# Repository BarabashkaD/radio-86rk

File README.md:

# Radio 86RK
Re-make of the Soviet Ham Radio computer published in Radio Magazine in 1986

## Hardware Documentation

## Table of Content
* [Introduction](#introduction)
* [Specifications](#specifications)
* [Verification](#verification)
* [KiCad 10](#kicad-10)
  * [Prerequisites](#prerequisites)
  * [Mechanical export, for case design](#mechanical-export-for-case-design)
* [Project Notes](#project-notes)
* [Hardware Documentation](#hardware-documentation)
  * [Schematic and PCB Layout](#schematic-and-pcb-layout)
  * [Connectors](#connectors)
  * [Bill of Materials](#bill-of-materials)
  * [Memory Map](#memory-map)
* [Firmware Documentation](#firmware-documentation)
  * [Monitor](#monitor)
* [Release Notes](#release-notes)
  * [Changes](#changes)
  * [Known Issues](#known-issues)

## Introduction
This project is a remake of [Radio-86RK](https://en.wikipedia.org/wiki/Radio-86RK) - a soviet ham radio computer. The original design was published in Radio Magazine, an amateur radio and DIY electronics oriented publication, starting from [April 1986](Radio-86RK_Publications.md). Hence the "Radio" and "86" in the name ("RK" stands for ham radio computer).

The goal of the original design was to create a computer that can be built relatively easily and cheaply using commonly available components. Therefore it included several short-cuts. For example it didn't use 8228 bus controller. Instead, it uses */WR* and *DBIN* CPU signals instead to distinguish between write and read CPU cycles. Since the system doesn't decode I/O control signals, all the I/O devices are memory mapped. Another optimization is the use of DMA controller for both supplying the data to the CRT controller and for refreshing DRAMs. The system didn't support interrupts. The sound was implemented using *INTE* output of the CPU. The software would use **EI**/**DI** instructions to generate sound. There are no graphics capabilities. The font size was limited to 128 characters (8275 CRT controller limitation), and given that it had to support both Latin and Cyrillic ABCs, it only had capital letters for both ABCs. The CRT controller shares 16 MHz clock oscillator with the CPU (not uncommon in other home computers at that time period).

Despite the limitations, the design was fairly successful, many people have built this computer, and there are some that still building one, this project included. In addtion, several factories manufactured computers based on (but not always compatible with) this design - e.g. [Mikrosha](https://oldcomputer.info/8bit/mikrosha/index.htm), [Apogee BK-01](https://ru.wikipedia.org/wiki/%D0%90%D0%BF%D0%BE%D0%B3%D0%B5%D0%B9_%D0%91%D0%9A-01), and a few more.

### Specifications of the Original Design
  * KR580VM80A (Intel 8080) CPU @ 1.78 MHz (16 MHz divided by 9)
  * 16 KiB to 32 KiB DRAM, 2 KiB ROM (monitor software)
  * KR580VG75 (Intel 8275) CRT controller which works together with KR580VT57 (Intel 8257) DMA controller. 1 KiB ROM is used for font
  * Two KR580VV55A (Intel 8255A) PPIs. One is used for keyboard and cassette I/O, another one for the extension port
  * Normally the computer consisted of 2 or 3 PCBs - the mainboard, the keyboard, and the keypad.

### Modifications to the Original Design
 * 16 DRAM ICs replaced with a single 32 KiB SRAM IC
 * Font ROM size increased to 2 KiB, so that it fits an alternative font. CRT controller GPA0 attribute is used to switch between fonts.
 * Reverse video attribute implemented in CRT controller
 * Added 8251 USART and 8253 timer. The timer is used for dividing the clock for USART and for sound generation.
 * Single board design, including an integrated mechanical keyboard
 * The work is largely based on [Radio-86RК-SRAM](http://radio86rk.pbworks.com/w/page/58467718/Radio-86R%D0%9A-SRAM) project created by Alexey Khudyakov (alexcp).

## Specifications
* Processor: Intel 8080A / КР580ВМ80А CPU running at 1.78 MHz
* Memory:
  * RAM: 32 KiB SRAM
  * ROM: 2 KiB UV EPROM with system monitor software
* Video: Intel 8275 / КР580ВГ75 CRT Controller
  * Alphanumeric display
  * 2 KiB UV EPROM with font
  * Composite video output (50 Hz)
* Audio:
  * Intel 8253 / КР580ВИ53 (single channel)
  * CPU INTE output
* Parallel Interface:
  * Intel 8255А / КР580ВВ55А PPI
  * 26-pin expansion header
* Serial Interface:
  * Intel 8251А / КР580ВВ51А USART
  * DE-9 connector
* Built-in 67-keys keyboard
* Cassette recorder interface

## Verification

This repository includes a small, dependency-free harness that proves the
board's copper, connectivity and rule counts have not changed since the
committed baseline. Requires KiCad 10+ and Python 3.8+, no install step:

```
python3 tools/kicad-verify.py all
```

See [`tools/README.md`](tools/README.md) for the full command reference,
exit codes, and how to reuse it on another project.

## KiCad 10

This fork's KiCad files have been modernized to KiCad 10 format. **The board is
unchanged**: the gerber and drill output is identical to skiselev's v1.4, verified
automatically rather than asserted. All footprints and symbols are vendored into the
repository, so the project opens from a fresh clone with no external checkouts.

The rear panel, with every external connector in one row — composite video, serial,
parallel, cassette, sound and power:

Also rendered: [top](images/Radio-86RK-1.4-3D-Top.jpg) ·
[from the right](images/Radio-86RK-1.4-3D-Iso-Right.jpg) ·
[solder side](images/Radio-86RK-1.4-3D-Bottom.jpg), which carries the memory map, the
monitor command list and the subroutine table in silkscreen.

### Prerequisites

* **KiCad 10.0.4** or newer.
* The **Keyswitch Kicad Library**, v2.4, from KiCad's Plugin and Content Manager —
  package `com.github.perigoso.keyswitch-kicad-library`, upstream
  [github.com/kiswitch/keyswitch-kicad-library](https://github.com/kiswitch/keyswitch-kicad-library),
  CC-BY-SA-4.0. It supplies three model files that 69 of this board's 209 model
  references depend on: the Cherry MX switch body shared by all 67 keys, and two
  stabilizers. Without it the board still opens, routes and exports correctly — only the
  keyboard renders empty in the 3D view.

Check that everything resolves before trusting a render:

```
python3 tools/kicad-verify.py models
```

It reports 183 / 183 footprints covered when the library is installed, and names the
path variable responsible when it is not.

- [Modernization summary](docs/modernization-summary.md) — before/after, and how to re-verify
- [3D model sources](docs/3d-model-sources.md) — every model choice and substitution
- [Retained DRC violations](docs/drc-exclusions.md) — the 22 inherited from v1.4
- [Retained ERC violations](docs/erc-exclusions.md) — the 32 bus-label warnings
- [3D model follow-ups](docs/followup-3d-models.md) — the five approximations now resolved, and optional keycaps

### Mechanical export, for case design

```
python3 tools/export_mech.py            # STEP + placement CSV into .build/mech/
```

Writes four STEP files sharing one datum — the whole assembly, the parts needing panel
cutouts, the switches alone, and the bare board with its mounting holes — plus a CSV
giving every footprint's position, rotation, value and package.

Keycaps are deliberately absent. A cap is a case parameter rather than a board one: its
envelope drives the top-plate openings and the bezel height, and comparing profiles should
cost one filename, not a re-export. `placement.csv`'s `Package` column is the cap size, so
all 68 caps can be placed from the table.

## Project Notes

Check [Project Notes](Project_Notes.md) for the information about building this project

## Hardware Documentation

### Documentation for the Previous Versions

* [Version 1.3](https://github.com/skiselev/radio-86rk/tree/v1.3)
* [Version 1.2](https://github.com/skiselev/radio-86rk/tree/v1.2)
* [Version 1.1](https://github.com/skiselev/radio-86rk/tree/v1.1)

### Schematic and PCB Layout

* [Schematic - Version 1.4](KiCad/Radio-86RK-Schematic-1.4.pdf)
* [PCB Layout - Version 1.4](KiCad/Radio-86RK-Board-1.4.pdf)

### Connectors

#### J1 - Composite Video

Pin | Description     
--- | ---------------
Tip (the inner contact) | Output: Composite Video
Ring / Sleeve         |	Power: GND

#### J2 - Power (5V)
Connect regulated +5V power supply to this connector.

Note: The 8080A CPU, clock generator, and serial port transmitters and receivers use +12V/-5V/-12V voltages. An on-board DC-DC converter (U26) is used to obtain these voltages. Instead of using the DC-DC converter it is possible to provide these voltages directly to the system using J3 connector.

Pin | Description     
--- | ---------------
Tip (the inner contact) | Power: 5V (positive terminal)
Barrel / Sleeve         |	Power: GND (negative terminal)

#### J3 - Power (5V, 12V, -12V)
Connect regulated 5V/12V/-12V power supply to this connector.

Pin | Description     
--- | ---------------
1, 2, 3 | Power: GND
4, 5, 6 |	Power: 5V
7   |	Power: 12V
8   |	Power: -12V

#### J4 - Cassette Connector
Pin | Description     
--- | ---------------
1, 2, 3, 8   | Power: GND
4   |	Output: Sound output to cassette recorder (line level)
5   |	Input: Sound input from cassette recorder (line level)
6, 7 |	Not connected

#### J5 - Serial Port Connector
Pin | Description     
--- | ---------------
1   | Not connected: DCD
2   | Input: RX
3   | Output: TX
4   | Output: DTR
5   | Power: GND
6   | Input: DSR
7   | Output: RTS
8   | Input: CTS
9   | Not connected: RI

#### J6 - Parallel Port Connector
Pin | Description | Pin | Description
--- | ----------- | --- | ----------------
1   | Output: PC0 | 2   | Input: PA0
3   | Output: PC1 | 4   | Input: PA1
5   | Output: PC2 | 6   | Input: PA2
7   | Output: PC3 | 8   | Input: PA3
9   | Output: PC4 | 10  | Input: PA4
11  | Output: PC5 | 12  | Input: PA5
13  | Output: PC6 | 14  | Input: PA6
15  | Output: PC7 | 16  | Input: PA7
17  | Output: PB7 | 18  | Output: PB0
19  | Output: PB6 | 20  | Output: PB1
21  | Output: PB5 | 22  | Output: PB2
23  | Output: PB4 | 24  | Output: PB3
25  | Power: +5V  | 26  | Power: GND

### Bill of Materials

* [Radio-86RK project on Mouser.com](https://www.mouser.com/ProjectManager/ProjectDetail.aspx?AccessID=d3d8f92a02) - View and order all components except of the PCB, and most Intel 8xxx ICs.

* [Unicorn Electronics](https://www.unicornelectronics.com/prod.htm) is a good source for Intel 8xxx or compatible ICs, 7400-series TTL ICs, and 74LS00-series TTL-LS ICs

Component type     | Reference | Description                                 | Quantity | Possible sources and notes
------------------ | --------- | ------------------------------------------- | -------- | --------------------------
PCB                |           | Radio-86RK PCB                              | 1        | Buy from my Tindie store: [Radio-86RK - PCB](https://www.tindie.com/products/weird/radio-86rk-pcb/) or order from a PCB manufacturer of your choice using provided Gerber or KiCad files
Capacitor          | C1 - C32  | 0.1 uF, MLCC, 5 mm Pitch                    | 32       | Mouser [594-K104K15X7RF53H5](https://www.mouser.com/ProductDetail/594-K104K15X7RF53H5)
Capacitor          | C33 - C38 | 47 uF, 25V, Electrolytic or Organic Polymer | 6 	      | Mouser [80-A750EK476M1EAAE40](https://www.mouser.com/ProductDetail/80-A750EK476M1EAAE40)
Capacitor          | C39       | 0.22 uF, MLCC, 5 mm Pitch                   | 1        | Mouser [810-FG24X7R1H224KNT0](https://www.mouser.com/ProductDetail/810-FG24X7R1H224KNT0)
Capacitor          | C40       | 22 nF, MLCC, 5 mm Pitch                     | 1        | Mouser [810-FG28X7R1H223KNT0](https://www.mouser.com/ProductDetail/810-FG28X7R1H223KNT0)
Capacitor          | C41       | 10 nF, MLCC, 5 mm Pitch                     | 1        | Mouser [810-FG28X7R1H103KNT0](https://www.mouser.com/ProductDetail/810-FG28X7R1H103KNT0)
Capacitor          | C42       | 2.2 nF, MLCC, 5 mm Pitch                    | 1        | Mouser [810-FG28X7R1H222KNT0](https://www.mouser.com/ProductDetail/810-FG28X7R1H222KNT0)
Capacitor          | C43       | 1 nF, MLCC, 5 mm Pitch                      | 1        | Mouser [810-FG28C0G1H102JNT6](https://www.mouser.com/ProductDetail/810-FG28C0G1H102JNT6)
Capacitor          | C44       | 10 pF, MLCC, 5 mm Pitch                     | 1        | Mouser [810-FG28C0G1H100DNT00](https://www.mouser.com/ProductDetail/810-FG28C0G1H100DNT0)
Diode              | D1 - D9  | 1N4148                                       | 9        | Mouser [512-1N4148](https://www.mouser.com/ProductDetail/512-1N4148)
LED                | D10       | LED Indicator, 3 mm, Green                  | 1        | Mouser [630-HLMP-1503-C0002](https://www.mouser.com/ProductDetail/630-HLMP-1503-C0002)
LED                | D11       | LED Indicator, 3 mm, Yellow                 | 1        | Mouser [630-HLMP-1401](https://www.mouser.com/ProductDetail/630-HLMP-1401)
Polyfuse           | F1        | 1.1A, 5 mm Pitch                            | 1        | Mouser [576-16R110BU](https://www.mouser.com/ProductDetail/576-16R110BU)
Connector          | JP1, JP2  | 4 pin header, 2.54 mm Pitch                 | 2        | Mouser [649-68000-204HLF](https://www.mouser.com/ProductDetail/649-68000-204HLF)
Connector          | JP1, JP2  | Jumper, 2.54 mm Pitch                       | 4        | Mouser [806-SX1100-B)](https://www.mouser.com/ProductDetail/806-SX1100-B)
Connector          | J1        | RCA Phono connector, Yellow                 | 1        | Mouser [490-RCJ-014](https://www.mouser.com/ProductDetail/490-RCJ-014)
Connector          | J2        | DC Power Jack, 2mm                          | 1        | Mouser [806-KLDX-0202-A](https://www.mouser.com/ProductDetail/806-KLDX-0202-A)
Connector          | J3        | 8 pin friction lock connector               | 1        | Mouser [571-6404568](https://www.mouser.com/ProductDetail/571-6404568)
Connector          | J4        | DIN 8-pos, Right Angle, PCB mount           | 1        | Mouser [490-SDF-80J](https://www.mouser.com/ProductDetail/490-SDF-80J)
Connector          | J5        | Sub-D DE9M, Right Angle, PCB mount          | 1        | Mouser [523-L717SDE09P1ACH3R](https://www.mouser.com/ProductDetail/523-L717SDE09P1ACH3R)
Connector          | J6        | 13x2 pin header, shrouded                   | 1        | Mouser [517-30326-6002](https://www.mouser.com/ProductDetail/517-30326-6002)
Connector          | J7        | 20x1 pin socket                             | 1        | Mouser [517-929850-01-20-RB](https://www.mouser.com/ProductDetail/517-929850-01-20-RB). Note: Optional, for extension board connection
Transistor         | Q1, Q2    | 2N3904                                      | 2        | Mouser [512-2N3904TA](https://www.mouser.com/ProductDetail/512-2N3904TA)
Resistor           | R1        | 33 ohm                                      | 1        | Mouser [660-CF1/4CT52R330J](https://www.mouser.com/ProductDetail/660-CF1-4CT52R330J)
Resistor           | R2        | 75 ohm                                      | 1        | Mouser [660-CF1/4CT52R750J](https://www.mouser.com/ProductDetail/660-CF1-4CT52R750J)
Resistor           | R3        | 150 ohm                                     | 1        | Mouser [660-CF1/4CT52R151J](https://www.mouser.com/ProductDetail/660-CF1-4CT52R151J)
Resistor           | R4        | 330 ohm                                     | 1        | Mouser [660-CF1/4CT52R331J](https://www.mouser.com/ProductDetail/660-CF1-4CT52R331J)
Resistor           | R5        | 1.5 k                                       | 1        | Mouser [660-CF1/4CT52R152J](https://www.mouser.com/ProductDetail/660-CF1-4CT52R152J)
Resistor           | R6 - R13  | 1 k                                         | 8        | Mouser [660-CF1/4CT52R102J](https://www.mouser.com/ProductDetail/660-CF1-4CT52R102J)
Resistor           | R14       | 2.4 k                                       | 1        | Mouser [660-CF1/4CT52R242J](https://www.mouser.com/ProductDetail/660-CF1-4CT52R242J)
Resistor           | R15       | 12 k                                        | 1        | Mouser [660-CF1/4CT52R123J](https://www.mouser.com/ProductDetail/660-CF1-4CT52R123J)
Resistor Array     | RN1       | 10 k, SIP10                                 | 1        | Mouser [652-4610X-1LF-10K](https://www.mouser.com/ProductDetail/652-4610X-1LF-10K)
Resistor Array     | RN2 - RN4 | 4.7 k, SIP6                                 | 3        | Mouser [652-4606X-1LF-4.7K](https://www.mouser.com/ProductDetail/652-4606X-1LF-4.7K)
Speaker            | SP1       | 12 mm speaker                               | 1        | Mouser [665-AT-1224TWTR](https://www.mouser.com/ProductDetail/665-AT-1224TWTR)
Keyboard Switch    | SW1 - SW67 | Cherry MX Blue (Clicky)                    | 67       | Mouser [540-MX1A-E1NW](https://www.mouser.com/ProductDetail/540-MX1A-E1NW)
Switch Leveling Kit | SW11, SW64 | Leveling kit for MX 1x2, 1x2.25, 1x2.75   | 2        | Mouser [540-G99-0742](https://www.mouser.com/ProductDetail/540-G99-0742)
Switch Leveling Kit | SW64     | Leveling kit for MX 1x8                     | 1        | Mouser [540-G99-0226](https://www.mouser.com/ProductDetail/540-G99-0226) Note: Use the wire from this part and one of 540-G99-0742 to build a through hole leveling kit for the spacebar
Tactile Switch     | SW68      | 6 mm Tactile Switch Right Angle             | 1        | Mouser [653-B3F-3152](https://www.mouser.com/ProductDetail/653-B3F-3152)
Switch Keycap      | SW68      | 4 x 4 mmm Tactile Switch Key Cap, Orange    | 1        | Mouser [653-B32-1020](https://www.mouser.com/ProductDetail/653-B32-1020)
Integrated Circuit | U1        | Intel 8080A / КР580ВМ80А, CPU               | 1        | Unicorn Electronics [8080A](https://www.unicornelectronics.com/IC/8000.html), Jameco [52046](https://www.jameco.com/z/8080A-Major-Brands-IC-8080A-8-Bit-MOS-MPU_52046.html)
Integrated Circuit | U2        | Intel 8224 / КР580ГФ24, Clock Generator     | 1        | Unicorn Electronics [8224](https://www.unicornelectronics.com/IC/8000.html)
Integrated Circuit | U3        | Intel 8251А / КР580ВВ51А, USART             | 1        | Unicorn Electronics [8251A](https://www.unicornelectronics.com/IC/8000.html)
Integrated Circuit | U4        | Intel 8253 / КР580ВИ53, PIT                 | 1        | Unicorn Electronics [8253](https://www.unicornelectronics.com/IC/8000.html), Mouser [968-CP82C54Z](https://www.mouser.com/ProductDetail/968-CP82C54Z)
Integrated Circuit | U5, U6    | Intel 8255А / КР580ВВ55А, PPI               | 2        | Unicorn Electronics [8055A](https://www.unicornelectronics.com/IC/8000.html), Mouser [968-CP82C55A-5Z](https://www.mouser.com/ProductDetail/968-CP82C55A-5Z), Jameco [52732](https://www.jameco.com/z/8255A-5-Major-Brands-IC-8255A-5-Programmable-Peripheral-Interface-40-pin-DIP_52732.html)
Integrated Circuit | U7        | Intel 8257 / КР580ВТ57, DMA Controller      | 1        | Unicorn Electronics [8257](https://www.unicornelectronics.com/IC/8000.html)
Integrated Circuit | U8        | Intel 8275 / КР580ВГ75, CRT Controller      | 1        | Unicorn Electronics [8275](https://www.unicornelectronics.com/IC/8000.html), Jameco [52821](https://www.jameco.com/z/8275-Major-Brands-Programmable-CRT-Controller-DIP-40_52821.html)
Integrated Circuit | U9        | AS6C62256, SRAM 32Kx8                       | 1        | Mouser [913-AS6C62256-55PCN](https://www.mouser.com/ProductDetail/913-AS6C62256-55PCN), Unicorn Electronics [62256LP](https://www.unicornelectronics.com/IC/STATIC.html)
Integrated Circuit | U10, U11  | 2716 / КР573РФ5, 2Kx8 EPROM                 | 2        | Mouser [556-AT28C64B15PU](https://www.mouser.com/ProductDetail/556-AT28C64B15PU), Unicorn Electronics [2716](https://www.unicornelectronics.com/IC/EPROM.html). Note: 2716, 2732, 2764, 27C64 EPROMs, or 28C64 EEPROMs can be used
Integrated Circuit | U12       | 74LS373/К555ИР22, 8-bit Latch, 3-state outputs | 1     | Mouser [595-SN74LS373N](https://www.mouser.com/ProductDetail/595-SN74LS373N)
Integrated Circuit | U13       | 74198/К155ИР13, 8-bit Shift Register        | 1        | Unicorn Electronics [74198](https://www.unicornelectronics.com/IC/7400.html)
Integrated Circuit | U14       | 74LS138/К555ИД7, Decoder 3 to 8 active low outputs | 1 | Mouser [595-SN74LS138N](https://www.mouser.com/ProductDetail/595-SN74LS138N), Unicorn Electronics [74LS138](https://www.unicornelectronics.com/IC/74LS.html)
Integrated Circuit | U15       | 7492/К155ИЕ4, Divide by 12 counter          | 1        | Mouser [595-SN74LS92N](https://www.mouser.com/ProductDetail/595-SN74LS92N), Unicorn Electronics [74LS92](https://www.unicornelectronics.com/IC/74LS.html)
Integrated Circuit | U16       | 7486/К155ЛП5, Quad 2-input XOR              | 1        | Mouser [595-SN74LS86AN](https://www.mouser.com/ProductDetail/595-SN74LS86AN), Unicorn Electronics [74LS86](https://www.unicornelectronics.com/IC/74LS.html)
Integrated Circuit | U17       | 7474/К155ТМ2, Dual D Flip-flop, Set & Reset | 1        | Mouser [595-SN74LS74AN](https://www.mouser.com/ProductDetail/595-SN74LS74AN), Unicorn Electronics [74LS74](https://www.unicornelectronics.com/IC/74LS.html)
Integrated Circuit | U18       | 7408/К155ЛИ1, Quad 2-input AND              | 1        | Mouser [595-SN74LS08N](https://www.mouser.com/ProductDetail/595-SN74LS08N), Unicorn Electronics [74LS08](https://www.unicornelectronics.com/IC/74LS.html)
Integrated Circuit | U19       | 7404/К155ЛН1, Hex Inverter                  | 1        | Mouser [595-SN74LS04N](https://www.mouser.com/ProductDetail/595-SN74LS04N), Unicorn Electronics [74LS04](https://www.unicornelectronics.com/IC/74LS.html)
Integrated Circuit | U20       | 7400/К155ЛА3, Quad 2-input NAND             | 1        | Mouser [595-SN74LS00N](https://www.mouser.com/ProductDetail/595-SN74LS00N), Unicorn Electronics [74LS00](https://www.unicornelectronics.com/IC/74LS.html)
Integrated Circuit | U21       | TL071/К140УД6, Operational Amplifier        | 1        | Mouser [595-TL071IP](https://www.mouser.com/ProductDetail/595-TL071IP)
Integrated Circuit | U22       | SN75154N/К170УП2В, Quad RS-232 Receiver     | 1        | Mouser [595-SN75154N](https://www.mouser.com/ProductDetail/595-SN75154N), Unicorn Electronics [75154](https://www.unicornelectronics.com/IC/INTERFACE.html)
Integrated Circuit | U23, U24  | SN75150P/К170АП2, Dual RS-232 Driver        | 2        | Mouser [595-SN75150P](https://www.mouser.com/ProductDetail/595-SN75150P), Unicorn Electronics [75150](https://www.unicornelectronics.com/IC/INTERFACE.html)
Integrated Circuit | U25       | LM7905/КР1179ЕНВ, Negative 5V 1A Linear Regulator | 1  | Mouser [926-LM7905CT-NOPB](https://www.mouser.com/ProductDetail/926-LM7905CT-NOPB), Unicorn Electronics [7905T](https://www.unicornelectronics.com/IC/VOLT.html)
DC-DC Converter    | U26       | IZ0512, +/-12V +/-125mA, 4.5V-9V input      | 1        | Mouser [209-IZ0512S](https://www.mouser.com/ProductDetail/209-IZ0512S)
Integrated Circuit | U27       | DS1233-5, CPU Supervisory Circuit           | 1        | Mouser [700-DS1233-5T&R](https://www.mouser.com/ProductDetail/700-DS1233-5TR)
Crystal            | Y1        | 16 MHz, Series, HC-49U                      | 1        | Mouser [774-ATS160-E](https://www.mouser.com/ProductDetail/774-ATS160-E)
IC Socket          | U1, U5, U6, U7, U8 | 40 pin DIP                         | 5        | Mouser [649-DILB40P223TLF](https://www.mouser.com/ProductDetail/649-DILB40P223TLF), [517-4840-6000-CP](https://www.mouser.com/ProductDetail/517-4840-6000-CP)
IC Socket          | U3, U9, U10, U11    | 28 pin DIP                                  | 4        | Mouser [649-DILB28P223TLF](https://www.mouser.com/ProductDetail/649-DILB28P223TLF), [517-4828-6000-CP](https://www.mouser.com/ProductDetail/517-4828-6000-CP)
IC Socket          | U4, U13   | 24 pin DIP                          | 2        | Mouser [649-DILB24P-223TLF](https://www.mouser.com/ProductDetail/649-DILB24P-223TLF), [517-4824-6000-CP](https://www.mouser.com/ProductDetail/517-4824-6000-CP)
IC Socket          | U12       | 20 pin DIP                                  | 1        | Mouser [649-DILB20P-223TLF](https://www.mouser.com/ProductDetail/649-DILB20P-223TLF), [517-4820-3000-CP](https://www.mouser.com/ProductDetail/517-4820-3000-CP)
IC Socket          | U2, U14, U22 | 16 pin DIP                               | 3        | Mouser [649-DILB16P-223TLF](https://www.mouser.com/ProductDetail/649-DILB16P-223TLF), [517-4816-3000-CP](https://www.mouser.com/ProductDetail/517-4816-3000-CP)
IC Socket          | U15 - U20 | 14 pin DIP                                  | 6        | Mouser [649-DILB14P-223TLF](https://www.mouser.com/ProductDetail/649-DILB14P-223TLF), [517-4814-3000-CP](https://www.mouser.com/ProductDetail/517-4814-3000-CP)
IC Socket          | U21, U23, U24 | 8 pin DIP                               | 3        | Mouser [649-DILB8P223TLF](https://www.mouser.com/ProductDetail/649-DILB8P223TLF), [517-4808-3000-CP](https://www.mouser.com/ProductDetail/517-4808-3000-CP)

### Memory Map
* 0000h - 7FFFh - SRAM
  * 7600h - 7FFFh - Display buffer and monitor variables
* 8000h - 8FFFh - 8255A PPI (Keyboard, Cassette recorder, Sound control)
  * 8000h - Channel A data
  * 8001h - Channel B data
  * 8002h - Channel C data
  * 8003h - Control word
* 9000h - 9FFFh - 8253 Timer (USART Clock, Sound)
  * 9000h - Channel 0 count
  * 9001h - Channel 1 count
  * 9002h - Channel 2 count
  * 9003h - Control word
* 0A000h - 0AFFFh - 8255A PPI (Parallel Interface)
  * 0A000h - Channel A data
  * 0A001h - Channel B data
  * 0A002h - Channel C data
  * 0A003h - Control word
* 0B000h - 0BFFFh - 8251A USART
  * 0B000h - Data register
  * 0B001h - Command register
* 0C000h - 0CFFFh - 8275 CRT Controller
* 0D000h - 0DFFFh - Unused
* 0E000h - 0EFFFh - 8257 DMA Controller (write only)
* 0E000h - 0FFFFh - Monitor EPROM (read only)

## Firmware Documentation

### Monitor

#### Monitor Commands
* Memory Operations
  * **D\<Start_Address\>,\<End_Address\>** - Display memory content in hexadecimal
  * **L\<Start_Address\>,\<End_Address\>** - Display memory content in ASCII
  * **F\<Start_Address\>,\<End_Address\>,\<Value\>** - Fill memory with the specified value
  * **M\<Address\>** - Modify memory content
  * **T\<Start_Address\>,\<End_Address\>,\<Destination_Start_Address\>** - Copy memory block to destination
  * **C\<Start_Address\>,\<End_Address\>,\<Destination_Start_Address\>** - Compare memory block with destination
  * **S\<Start_Address\>,\<End_Address\>,\<Value\>** - Search memory for a value
  * **R\<ROM_Start_Address\>,\<ROM_End_Address\>,\<Destination_Start_Address\>** - Read from the ROM connected to the Parallel interface to memory
* Run Control
  * **G\<Start_Address\>\[,End_Address\]** - Run code, optionally stop at the specified address
  * **X** - Display and modify registers
* Cassette Input/Output
  * **O\<Start_Address\>,\<End_Address\>\[,Speed\]** - Write memory to cassette. Default speed is 1Dh / 1200 bps
  * **I\[Offset\]\[,Speed\]** - Read data from to cassette memory at specified offset

#### Monitor Subroutines:
* 0F803h - Keyboard input
  * Input: None
  * Output: A - character code read from keyboard
* 0F806h - Cassette input
  * Input: A=0FFh - with sync; A=08h - no sync
  * Output: A - data read from cassette
* 0F809h - Print character to screen
  * Input: C - character to print
* 0F80Ch - Cassette output
  * Input: C - data to write
* 0F812h - Query keyboard
  * Output: A=00h - key not pressed; A=0FFh - key pressed
* 0F815h - Print to screen in hex
  * Input: A - data to print
* 0F818h - Print string
  * Input: HL - string address
* 0F81Bh - Get key
  * Output: A=0FFh - key not pressed; A=0FEh - Rus/Lat; otherwise A - key code
* 0F81Eh - Get cursor position
  * Output: H - row, L - column
* 0F821h - Read character from screen at current cursor position
  * Output: A - char read from screen
* 0F824h - Read from cassette
  * Input: HL - offset of memory buffer to store data to
  * Output: HL - start; DE - end; BC - checksum

## Release Notes

### Changes
* Version 1.4
  * Change keyboard layout to QWERTY
  * Add the J7 extension connector
  * Add support for 2732, 2764 and 27C64 EPROMs and 28C64 EEPROM.

* Version 1.3
  * Fix issues from version 1.1 and version 1.2:
    * Use key labels "Ь X" and "СС SHIFT" on top silkscreen
    * Video signal generation circuit: use R2 = 75 Ohm and R5 = 1.5 kOhm
    
* Version 1.2
  * Add F5 key
  * Add copyright year on the top silkscreen

* Version 1.1
  * Fix all known issues of version 1.0
  * Use DS1233-5 mircoprocessor supervisor to generate reset signal
  * Implement reverse video attribute

* Version 1.0
  * Initial version

### Known Issues
* Version 1.3
  * No known issues

* Version 1.2
  * Top silkscreen: "Ь" and "X" key labels are swapped
  * Top silkscreen: More correct translation for "СС" is "SHIFT"
  * Video signal generation: Produced video Vpp and the backporch levels are a bit too high. Use R2 = 75 to 100 Ohm, and R5 = 1.5 kOhm for proper video signal levels (Reported by Martin Lukasek)
* Version 1.1
  * Top silkscreen: "Ь" and "X" key labels are swapped
  * Top silkscreen: More correct translation for "СС" is "SHIFT"
  * Top silkscreen: No copyright year
  * Video signal generation: Produced video Vpp and the backporch levels are a bit too high. Use R2 = 75 to 100 Ohm, and R5 = 1.5 kOhm for proper video signal levels (Reported by Martin Lukasek)

* Version 1.0
  * 8224 (U2) should use DIP-16 footprint
  * Down and Right buttons swapped
  * Reset RC does not provide enough time for the system to properly reset at power-on

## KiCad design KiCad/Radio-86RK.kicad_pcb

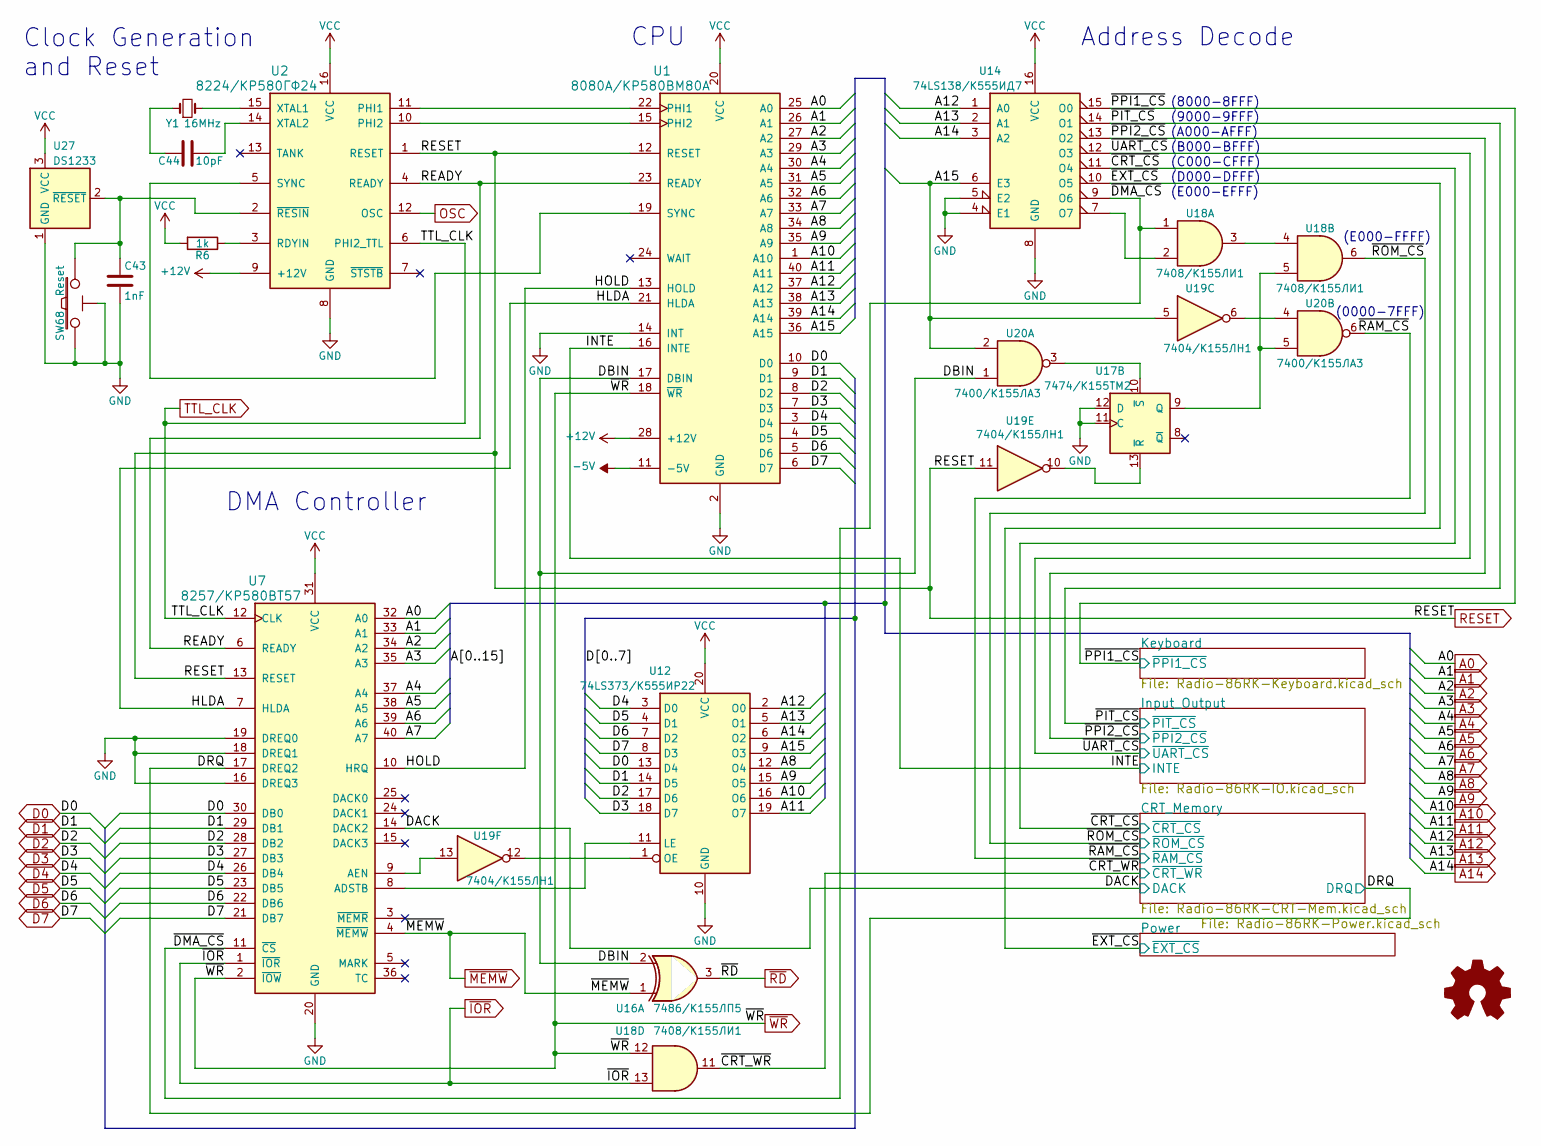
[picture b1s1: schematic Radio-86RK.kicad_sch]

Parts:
C43: 1nF; Cap_Cer_508
C44: 10pF; Cap_Cer_508
LOGO1: Logo_Open_Hardware_Small; KiCad-Logo2_6mm_SilkScreen
R6: 1k; Res_762
SW68: Reset; Switch_Tactile_6mm_Right
U1: 8080A/КР580ВМ80А; IC_DIP40_600
U2: 8224/КР580ГФ24; IC_DIP16_300
U7: 8257/КР580ВТ57; IC_DIP40_600
U12: 74LS373/К555ИР22; IC_DIP20_300
U14: 74LS138/К555ИД7; IC_DIP16_300
U16: 7486/К155ЛП5; IC_DIP14_300
U17: 7474/К155ТМ2; IC_DIP14_300
U18: 7408/К155ЛИ1; IC_DIP14_300
U19: 7404/К155ЛН1; IC_DIP14_300
U20: 7400/К155ЛА3; IC_DIP14_300
U27: DS1233; Transistor_TO92_EBC_254
Y1: 16MHz; Crystal_HC-49U_Vert

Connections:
+12V: U1.28 (+12V), U2.9 (+12V); also elsewhere on the board
-5V: U1.11 (-5V); also elsewhere on the board
/A15: U1.36 (A15), U12.9 (O3), U14.6 (E3), U19.5, U20.2
/DACK: U7.14 (DACK2); also elsewhere on the board
/DBIN: U1.17 (DBIN), U16.2, U20.1
/DRQ: U7.17 (DREQ2); also elsewhere on the board
/HLDA: U1.21 (HLDA), U7.7 (HLDA)
/HOLD: U1.13 (HOLD), U7.10 (HRQ)
/INTE: U1.16 (INTE); also elsewhere on the board
/READY: U1.23 (READY), U2.4 (READY), U7.6 (READY)
/~CRT_CS: U14.11 (O4); also elsewhere on the board
/~CRT_WR: U18.11; also elsewhere on the board
/~DMA_CS: U7.11 (~CS), U14.9 (O6), U18.1
/~EXT_CS: U14.10 (O5); also elsewhere on the board
/~PIT_CS: U14.14 (O1); also elsewhere on the board
/~PPI1_CS: U14.15 (O0); also elsewhere on the board
/~PPI2_CS: U14.13 (O2); also elsewhere on the board
/~RAM_CS: U20.6; also elsewhere on the board
/~ROM_CS: U18.6; also elsewhere on the board
/~UART_CS: U14.12 (O3); also elsewhere on the board
A0: U1.25 (A0), U7.32 (A0); also elsewhere on the board
A1: U1.26 (A1), U7.33 (A1); also elsewhere on the board
A2: U1.27 (A2), U7.34 (A2); also elsewhere on the board
A3: U1.29 (A3), U7.35 (A3); also elsewhere on the board
A4: U1.30 (A4), U7.37 (A4); also elsewhere on the board
A5: U1.31 (A5), U7.38 (A5); also elsewhere on the board
A6: U1.32 (A6), U7.39 (A6); also elsewhere on the board
A7: U1.33 (A7), U7.40 (A7); also elsewhere on the board
A8: U1.34 (A8), U12.12 (O4); also elsewhere on the board
A9: U1.35 (A9), U12.15 (O5); also elsewhere on the board
A10: U1.1 (A10), U12.16 (O6); also elsewhere on the board
A11: U1.40 (A11), U12.19 (O7); also elsewhere on the board
A12: U1.37 (A12), U12.2 (O0), U14.1 (A0); also elsewhere on the board
A13: U1.38 (A13), U12.5 (O1), U14.2 (A1); also elsewhere on the board
A14: U1.39 (A14), U12.6 (O2), U14.3 (A2); also elsewhere on the board
D0: U1.10 (D0), U7.30 (DB0), U12.13 (D4); also elsewhere on the board
D1: U1.9 (D1), U7.29 (DB1), U12.14 (D5); also elsewhere on the board
D2: U1.8 (D2), U7.28 (DB2), U12.17 (D6); also elsewhere on the board
D3: U1.7 (D3), U7.27 (DB3), U12.18 (D7); also elsewhere on the board
D4: U1.3 (D4), U7.26 (DB4), U12.3 (D0); also elsewhere on the board
D5: U1.4 (D5), U7.23 (DB5), U12.4 (D1); also elsewhere on the board
D6: U1.5 (D6), U7.22 (DB6), U12.7 (D2); also elsewhere on the board
D7: U1.6 (D7), U7.21 (DB7), U12.8 (D3); also elsewhere on the board
GND: C43.2, SW68.2, SW68.GND, U1.2 (GND), U1.14 (INT), U2.8 (GND), U7.16 (DREQ3), U7.18 (DREQ1), U7.19 (DREQ0), U7.20 (GND), U12.10 (GND), U14.4 (E1), U14.5 (E2), U14.8 (GND), U17.11 (C), U17.12 (D), U27.1 (GND); also elsewhere on the board
unnamed: C43.1, SW68.1, U2.2 (~RESIN), U27.2 (~RESET)
unnamed: C44.1, U2.14 (XTAL2)
unnamed: C44.2, Y1.1
unnamed: R6.1, U2.3 (RDYIN)
unnamed: U1.15 (PHI2), U2.10 (PHI2)
unnamed: U1.19 (SYNC), U2.5 (SYNC)
unnamed: U1.22 (PHI1), U2.11 (PHI1)
unnamed: U2.15 (XTAL1), Y1.2
unnamed: U12.1 (OE), U19.12
unnamed: U7.8 (ADSTB), U12.11 (LE)
unnamed: U14.7 (O7), U18.2
unnamed: U17.9 (Q), U18.5, U20.5
unnamed: U17.10 (~S), U20.3
unnamed: U17.13 (~R), U19.10
unnamed: U18.3, U18.4
unnamed: U19.6, U20.4
unnamed: U7.9 (AEN), U19.13
OSC: U2.12 (OSC); also elsewhere on the board
RESET: U1.12 (RESET), U2.1 (RESET), U7.13 (RESET), U19.11; also elsewhere on the board
TTL_CLK: U2.6 (PHI2_TTL), U7.12 (CLK); also elsewhere on the board
VCC: R6.2, U1.20 (VCC), U2.16 (VCC), U7.31 (VCC), U12.20 (VCC), U14.16 (VCC), U27.3 (VCC); also elsewhere on the board
~IOR: U7.1 (~IOR), U18.13; also elsewhere on the board
~MEMW: U7.4 (~MEMW), U16.1; also elsewhere on the board
~RD: U16.3; also elsewhere on the board
~WR: U1.18 (~WR), U7.2 (~IOW), U18.12; also elsewhere on the board

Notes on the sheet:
CPU
(E000-FFFF)
(8000-8FFF)
Clock Generation and Reset
(B000-BFFF)
(C000-CFFF)
(0000-7FFF)
(9000-9FFF)
Address Decode
(E000-EFFF)
(A000-AFFF)
DMA Controller
(D000-DFFF)

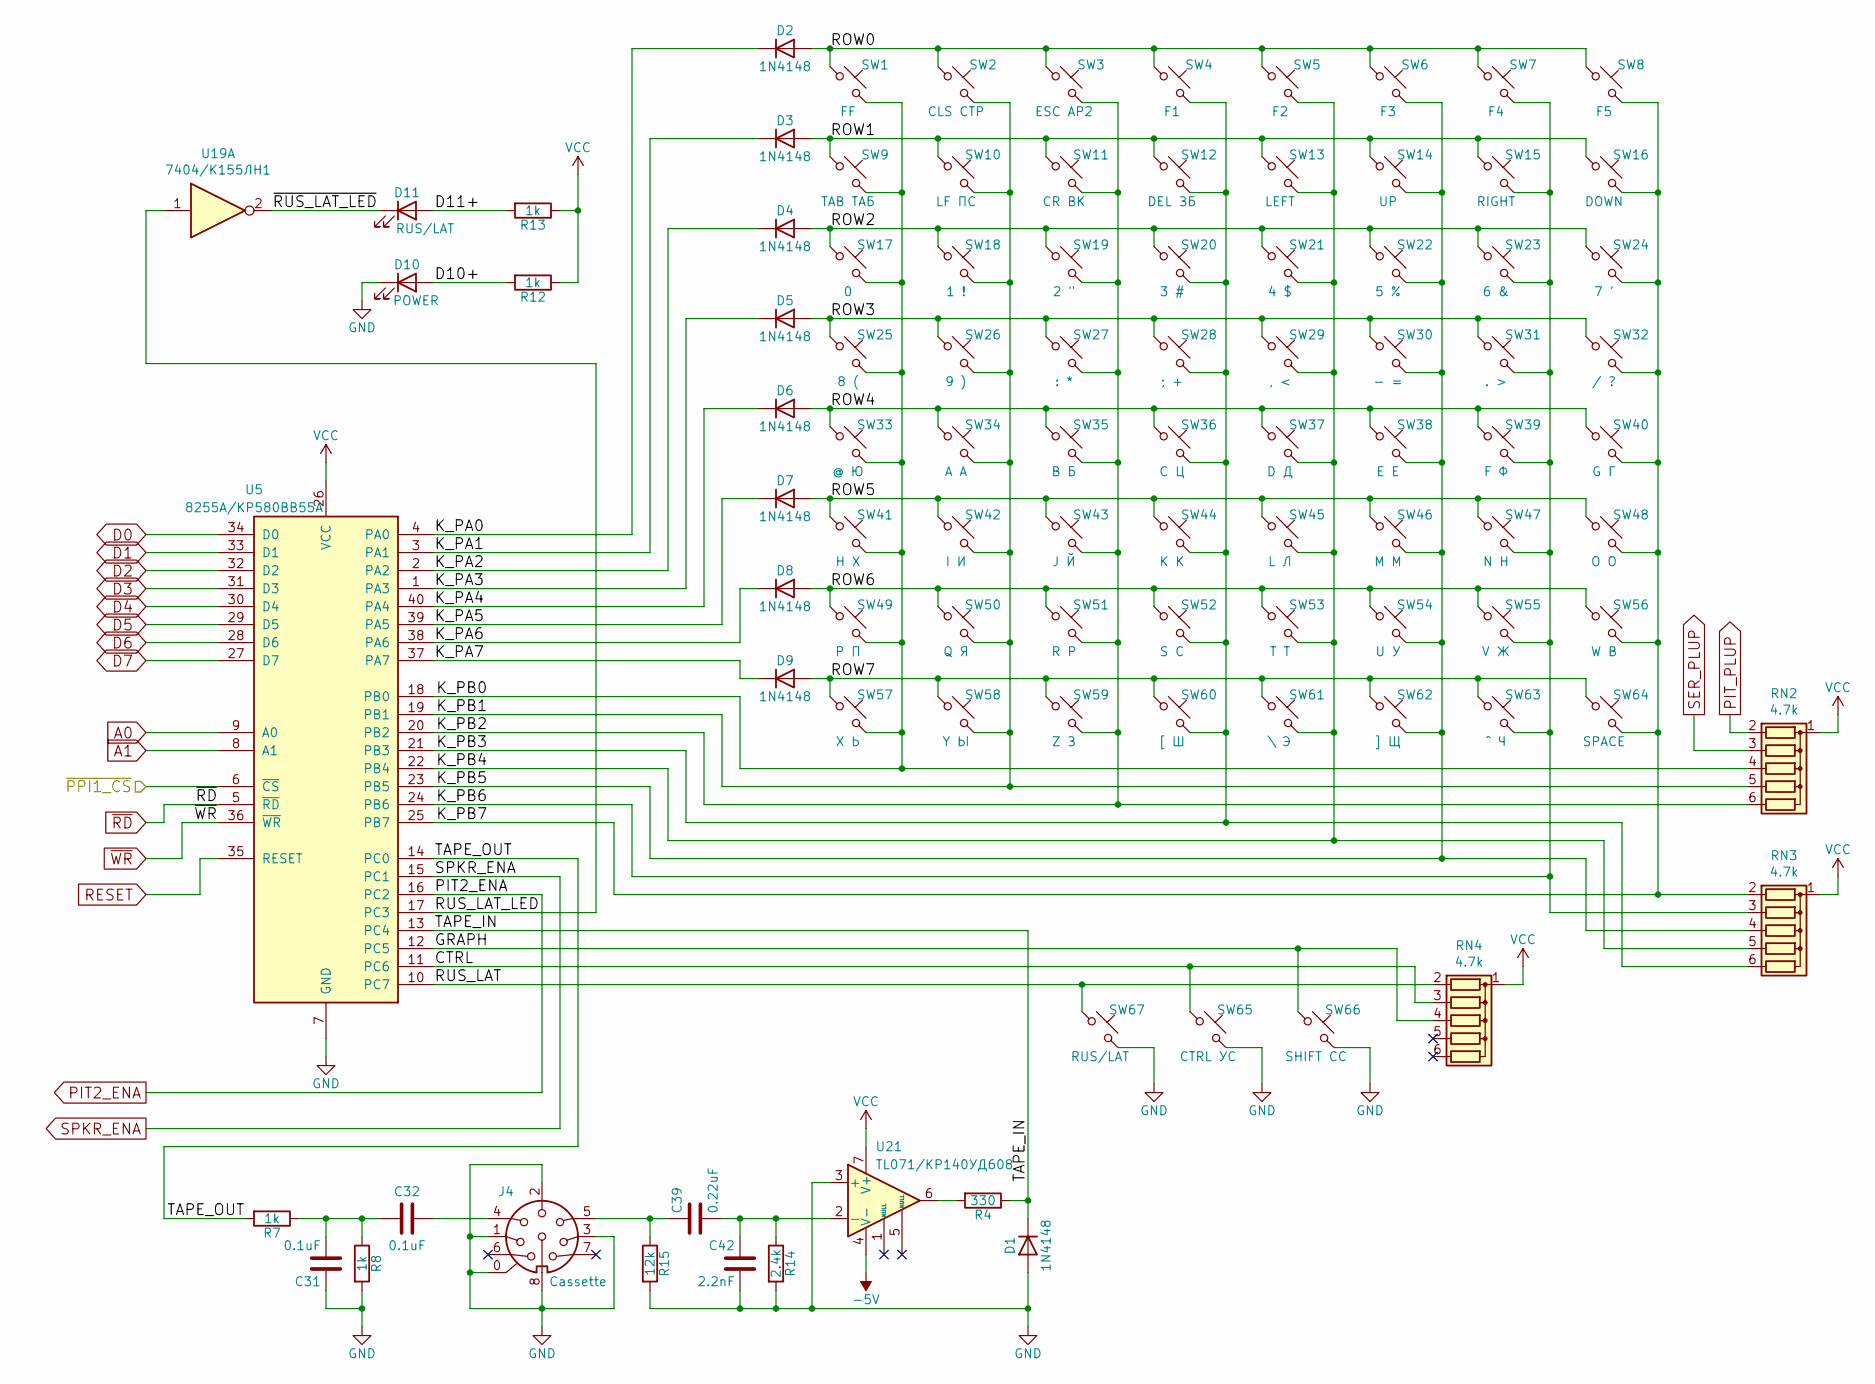
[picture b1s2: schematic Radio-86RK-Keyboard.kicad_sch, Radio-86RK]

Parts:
C31, C32: 0.1uF; Cap_Cer_508
C39: 0.22uF; Cap_Cer_508
C42: 2.2nF; Cap_Cer_508
D1, D2, D3, D4, D5, D6, D7, D8, D9: 1N4148; Diode_762
D10: POWER; LED_3mm
D11: RUS/LAT; LED_3mm
J4: Cassette; Conn_DIN_8pin
R4: 330; Res_762
R7, R8, R12, R13: 1k; Res_762
R14: 2.4k; Res_762
R15: 12k; Res_762
RN2, RN3, RN4: 4.7k; Conn_SIL6
SW1: FF; CHERRY_PCB_100H
SW2: CLS СТР; CHERRY_PCB_100H
SW3: ESC АР2; CHERRY_PCB_100H
SW4: F1; CHERRY_PCB_100H
SW5: F2; CHERRY_PCB_100H
SW6: F3; CHERRY_PCB_100H
SW7: F4; CHERRY_PCB_100H
SW8: F5; CHERRY_PCB_100H
SW9: TAB ТАБ; CHERRY_PCB_100H
SW10: LF ПС; CHERRY_PCB_100H
SW11: CR ВК; CHERRY_PCB_225H
SW12: DEL ЗБ; CHERRY_PCB_100H
SW13: LEFT; CHERRY_PCB_100H
SW14: UP; CHERRY_PCB_100H
SW15: RIGHT; CHERRY_PCB_100H
SW16: DOWN; CHERRY_PCB_100H
SW17: 0; CHERRY_PCB_100H
SW18: 1 !; CHERRY_PCB_100H
SW19: 2 "; CHERRY_PCB_100H
SW20: 3 #; CHERRY_PCB_100H
SW21: 4 $; CHERRY_PCB_100H
SW22: 5 %; CHERRY_PCB_100H
SW23: 6 &; CHERRY_PCB_100H
SW24: 7 '; CHERRY_PCB_100H
SW25: 8 (; CHERRY_PCB_100H
SW26: 9 ); CHERRY_PCB_100H
SW27: : *; CHERRY_PCB_100H
SW28: ; +; CHERRY_PCB_100H
SW29: , <; CHERRY_PCB_100H
SW30: - =; CHERRY_PCB_100H
SW31: . >; CHERRY_PCB_100H
SW32: / ?; CHERRY_PCB_100H
SW33: @ Ю; CHERRY_PCB_100H
SW34: A А; CHERRY_PCB_100H
SW35: B Б; CHERRY_PCB_100H
SW36: C Ц; CHERRY_PCB_100H
SW37: D Д; CHERRY_PCB_100H
SW38: E Е; CHERRY_PCB_100H
SW39: F Ф; CHERRY_PCB_100H
SW40: G Г; CHERRY_PCB_100H
SW41: H Х; CHERRY_PCB_100H
SW42: I И; CHERRY_PCB_100H
SW43: J Й; CHERRY_PCB_100H
SW44: K К; CHERRY_PCB_100H
SW45: L Л; CHERRY_PCB_100H
SW46: M М; CHERRY_PCB_100H
SW47: N Н; CHERRY_PCB_100H
SW48: O О; CHERRY_PCB_100H
SW49: P П; CHERRY_PCB_100H
SW50: Q Я; CHERRY_PCB_100H
SW51: R Р; CHERRY_PCB_100H
SW52: S С; CHERRY_PCB_100H
SW53: T Т; CHERRY_PCB_100H
SW54: U У; CHERRY_PCB_100H
SW55: V Ж; CHERRY_PCB_100H
SW56: W В; CHERRY_PCB_100H
SW57: X Ь; CHERRY_PCB_100H
SW58: Y Ы; CHERRY_PCB_100H
SW59: Z З; CHERRY_PCB_100H
SW60: [ Ш; CHERRY_PCB_100H
SW61: \ Э; CHERRY_PCB_150H
SW62: ] Щ; CHERRY_PCB_100H
SW63: ^ Ч; CHERRY_PCB_100H
SW64: SPACE; CHERRY_PCB_625H
SW65: CTRL УС; CHERRY_PCB_125H
SW66: SHIFT CC; CHERRY_PCB_125H
SW67: RUS/LAT; CHERRY_PCB_100H
U5: 8255A/КР580ВВ55А; IC_DIP40_600
U19: 7404/К155ЛН1; IC_DIP14_300
U21: TL071/КР140УД608; IC_DIP8_300

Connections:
-5V: U21.4 (V-); also elsewhere on the board
/Keyboard/CTRL: RN4.3 (R2), SW65.1, U5.11 (PC6)
/Keyboard/D10+: D10.2 (A), R12.2
/Keyboard/D11+: D11.2 (A), R13.2
/Keyboard/GRAPH: RN4.4 (R3), SW66.1, U5.12 (PC5)
/Keyboard/K_PA0: D2.1 (K), U5.4 (PA0)
/Keyboard/K_PA1: D3.1 (K), U5.3 (PA1)
/Keyboard/K_PA2: D4.1 (K), U5.2 (PA2)
/Keyboard/K_PA3: D5.1 (K), U5.1 (PA3)
/Keyboard/K_PA4: D6.1 (K), U5.40 (PA4)
/Keyboard/K_PA5: D7.1 (K), U5.39 (PA5)
/Keyboard/K_PA6: D8.1 (K), U5.38 (PA6)
/Keyboard/K_PA7: D9.1 (K), U5.37 (PA7)
/Keyboard/K_PB0: RN2.4 (R3), SW1.2, SW9.2, SW17.2, SW25.2, SW33.2, SW41.2, SW49.2, SW57.2, U5.18 (PB0)
/Keyboard/K_PB1: RN2.5 (R4), SW2.2, SW10.2, SW18.2, SW26.2, SW34.2, SW42.2, SW50.2, SW58.2, U5.19 (PB1)
/Keyboard/K_PB2: RN2.6 (R5), SW3.2, SW11.2, SW19.2, SW27.2, SW35.2, SW43.2, SW51.2, SW59.2, U5.20 (PB2)
/Keyboard/K_PB3: RN3.6 (R5), SW4.2, SW12.2, SW20.2, SW28.2, SW36.2, SW44.2, SW52.2, SW60.2, U5.21 (PB3)
/Keyboard/K_PB4: RN3.5 (R4), SW5.2, SW13.2, SW21.2, SW29.2, SW37.2, SW45.2, SW53.2, SW61.2, U5.22 (PB4)
/Keyboard/K_PB5: RN3.4 (R3), SW6.2, SW14.2, SW22.2, SW30.2, SW38.2, SW46.2, SW54.2, SW62.2, U5.23 (PB5)
/Keyboard/K_PB6: RN3.3 (R2), SW7.2, SW15.2, SW23.2, SW31.2, SW39.2, SW47.2, SW55.2, SW63.2, U5.24 (PB6)
/Keyboard/K_PB7: RN3.2 (R1), SW8.2, SW16.2, SW24.2, SW32.2, SW40.2, SW48.2, SW56.2, SW64.2, U5.25 (PB7)
/Keyboard/ROW0: D2.2 (A), SW1.1, SW2.1, SW3.1, SW4.1, SW5.1, SW6.1, SW7.1, SW8.1
/Keyboard/ROW1: D3.2 (A), SW9.1, SW10.1, SW11.1, SW12.1, SW13.1, SW14.1, SW15.1, SW16.1
/Keyboard/ROW2: D4.2 (A), SW17.1, SW18.1, SW19.1, SW20.1, SW21.1, SW22.1, SW23.1, SW24.1
/Keyboard/ROW3: D5.2 (A), SW25.1, SW26.1, SW27.1, SW28.1, SW29.1, SW30.1, SW31.1, SW32.1
/Keyboard/ROW4: D6.2 (A), SW33.1, SW34.1, SW35.1, SW36.1, SW37.1, SW38.1, SW39.1, SW40.1
/Keyboard/ROW5: D7.2 (A), SW41.1, SW42.1, SW43.1, SW44.1, SW45.1, SW46.1, SW47.1, SW48.1
/Keyboard/ROW6: D8.2 (A), SW49.1, SW50.1, SW51.1, SW52.1, SW53.1, SW54.1, SW55.1, SW56.1
/Keyboard/ROW7: D9.2 (A), SW57.1, SW58.1, SW59.1, SW60.1, SW61.1, SW62.1, SW63.1, SW64.1
/Keyboard/RUS_LAT: RN4.2 (R1), SW67.1, U5.10 (PC7)
/Keyboard/RUS_LAT_LED: U5.17 (PC3), U19.1
/Keyboard/TAPE_IN: D1.1 (K), R4.1, U5.13 (PC4)
/Keyboard/TAPE_OUT: R7.2, U5.14 (PC0)
/Keyboard/~RUS_LAT_LED: D11.1 (K), U19.2
/~PPI1_CS: U5.6 (~CS); also elsewhere on the board
A0: U5.9 (A0); also elsewhere on the board
A1: U5.8 (A1); also elsewhere on the board
D0: U5.34 (D0); also elsewhere on the board
D1: U5.33 (D1); also elsewhere on the board
D2: U5.32 (D2); also elsewhere on the board
D3: U5.31 (D3); also elsewhere on the board
D4: U5.30 (D4); also elsewhere on the board
D5: U5.29 (D5); also elsewhere on the board
D6: U5.28 (D6); also elsewhere on the board
D7: U5.27 (D7); also elsewhere on the board
GND: C31.1, C42.2, D1.2 (A), D10.1 (K), J4.0, J4.1, J4.2, J4.3, J4.8, R8.2, R14.2, R15.2, SW65.2, SW66.2, SW67.2, U5.7 (GND), U21.3 (+); also elsewhere on the board
unnamed: C31.2, C32.2, R7.1, R8.1
unnamed: C32.1, J4.4
unnamed: C39.1, J4.5, R15.1
unnamed: C39.2, C42.1, R14.1, U21.2 (-)
unnamed: R4.2, U21.6
PIT2_ENA: U5.16 (PC2); also elsewhere on the board
PIT_PLUP: RN2.2 (R1); also elsewhere on the board
RESET: U5.35 (RESET); also elsewhere on the board
SER_PLUP: RN2.3 (R2); also elsewhere on the board
SPKR_ENA: U5.15 (PC1); also elsewhere on the board
VCC: R12.1, R13.1, RN2.1 (common), RN3.1 (common), RN4.1 (common), U5.26 (VCC), U21.7 (V+); also elsewhere on the board
~RD: U5.5 (~RD); also elsewhere on the board
~WR: U5.36 (~WR); also elsewhere on the board

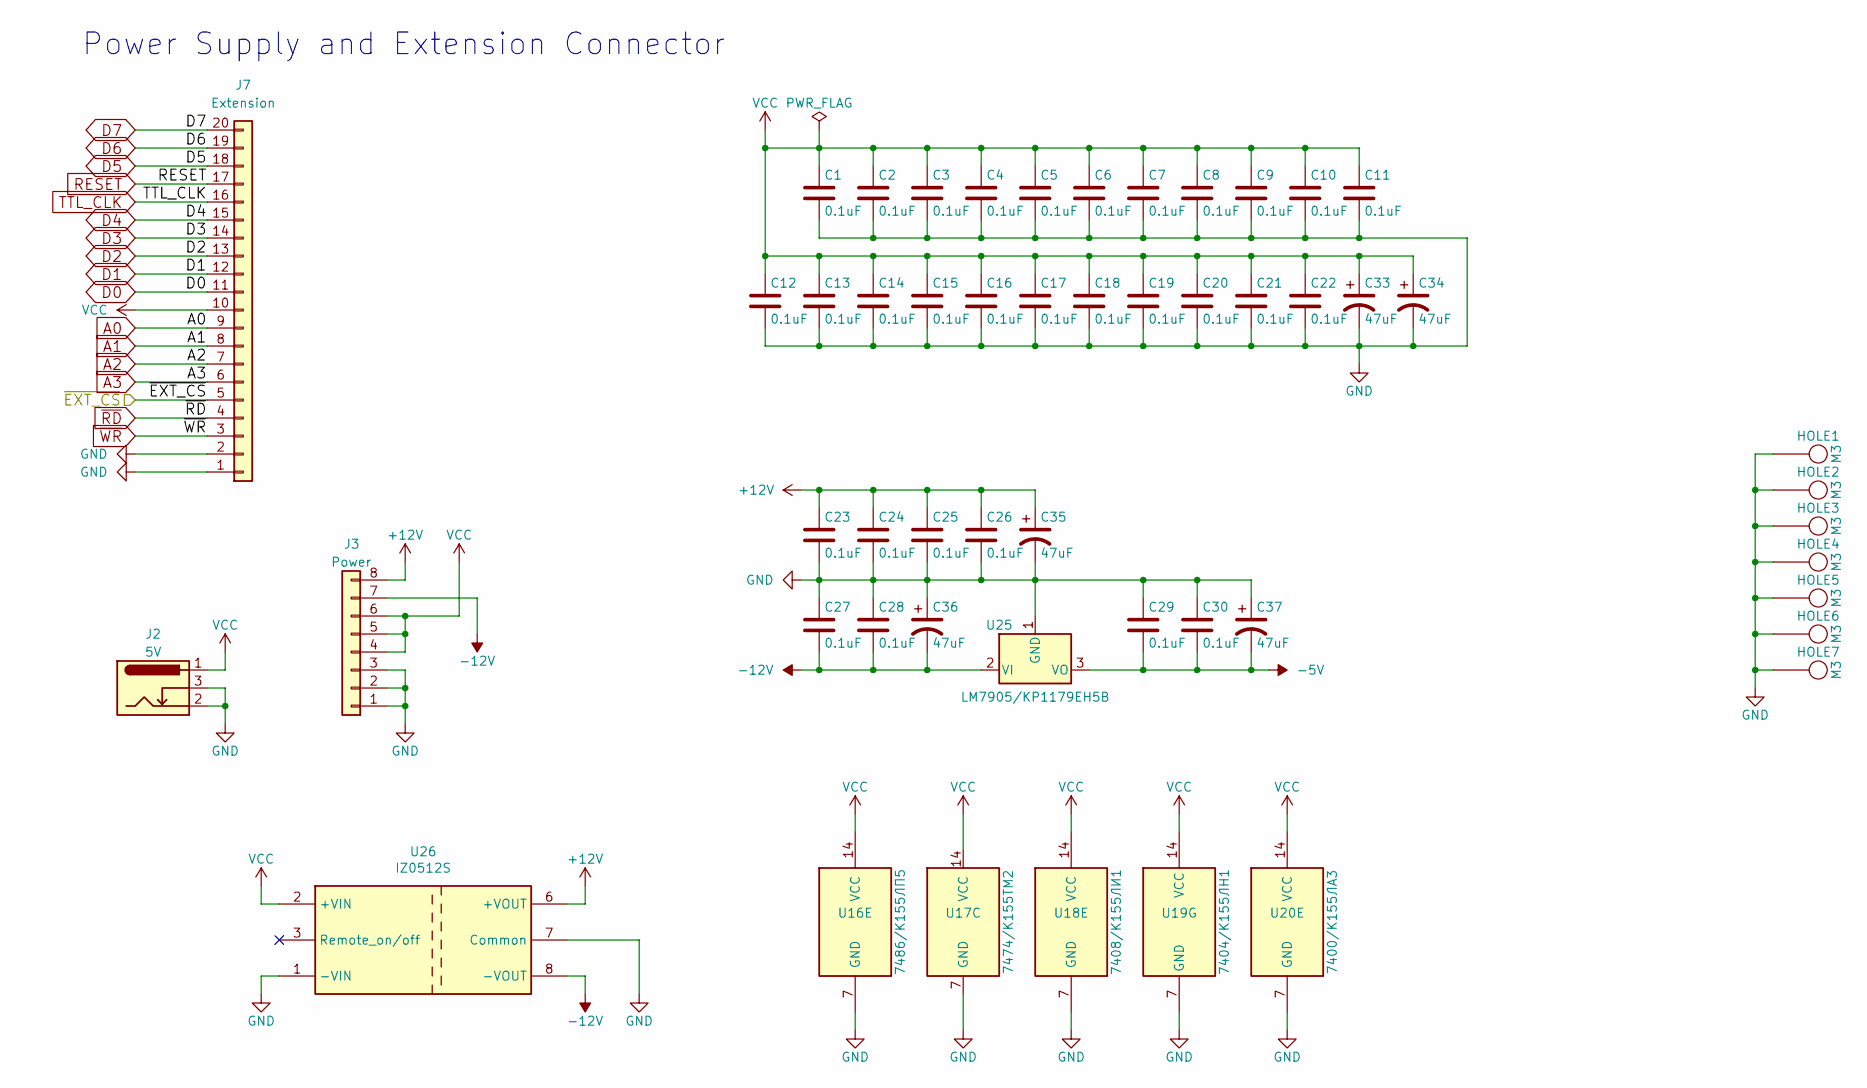
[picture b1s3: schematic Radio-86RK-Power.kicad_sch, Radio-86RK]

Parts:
C1, C2, C3, C4, C5, C6, C7, C8, C9, C10, C11, C12, C13, C14, C15, C16, C17, C18, C19, C20, C21, C22, C23, C24, C25, C26, C27, C28, C29, C30: 0.1uF; Cap_Cer_508
C33, C34, C35, C36, C37: 47uF; Cap_Elec_Radial_6.3mm
HOLE1, HOLE2, HOLE3, HOLE4, HOLE5, HOLE6, HOLE7: M3; Hole_3mm
J2: 5V; Conn_Power_Jack_Circular_Pads
J3: Power; Conn_Friction_Lock_8P_2.54mm
J7: Extension; Conn_Pin_Header_20x1_2.54mm
U16: 7486/К155ЛП5; IC_DIP14_300
U17: 7474/К155ТМ2; IC_DIP14_300
U18: 7408/К155ЛИ1; IC_DIP14_300
U19: 7404/К155ЛН1; IC_DIP14_300
U20: 7400/К155ЛА3; IC_DIP14_300
U25: LM7905/КР1179ЕН5В; IC_TO220-3_Vert
U26: IZ0512S; DC-DC_SIP8

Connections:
+12V: C23.1, C24.1, C25.1, C26.1, C35.1, J3.8, U26.6 (+VOUT); also elsewhere on the board
-5V: C29.2, C30.2, C37.2, U25.3 (VO); also elsewhere on the board
-12V: C27.2, C28.2, C36.2, J3.7, U25.2 (VI), U26.8 (-VOUT); also elsewhere on the board
/~EXT_CS: J7.5; also elsewhere on the board
A0: J7.9; also elsewhere on the board
A1: J7.8; also elsewhere on the board
A2: J7.7; also elsewhere on the board
A3: J7.6; also elsewhere on the board
D0: J7.11; also elsewhere on the board
D1: J7.12; also elsewhere on the board
D2: J7.13; also elsewhere on the board
D3: J7.14; also elsewhere on the board
D4: J7.15; also elsewhere on the board
D5: J7.18; also elsewhere on the board
D6: J7.19; also elsewhere on the board
D7: J7.20; also elsewhere on the board
GND: C1.2, C2.2, C3.2, C4.2, C5.2, C6.2, C7.2, C8.2, C9.2, C10.2, C11.2, C12.2, C13.2, C14.2, C15.2, C16.2, C17.2, C18.2, C19.2, C20.2, C21.2, C22.2, C23.2, C24.2, C25.2, C26.2, C27.1, C28.1, C29.1, C30.1, C33.2, C34.2, C35.2, C36.1, C37.1, HOLE1.1, HOLE2.1, HOLE3.1, HOLE4.1, HOLE5.1, HOLE6.1, HOLE7.1, J2.2, J2.3, J3.1, J3.2, J3.3, J7.1, J7.2, U16.7 (GND), U17.7 (GND), U18.7 (GND), U19.7 (GND), U20.7 (GND), U25.1 (GND), U26.1 (-VIN), U26.7 (Common); also elsewhere on the board
RESET: J7.17; also elsewhere on the board
TTL_CLK: J7.16; also elsewhere on the board
VCC: C1.1, C2.1, C3.1, C4.1, C5.1, C6.1, C7.1, C8.1, C9.1, C10.1, C11.1, C12.1, C13.1, C14.1, C15.1, C16.1, C17.1, C18.1, C19.1, C20.1, C21.1, C22.1, C33.1, C34.1, J2.1, J3.4, J3.5, J3.6, J7.10, U16.14 (VCC), U17.14 (VCC), U18.14 (VCC), U19.14 (VCC), U20.14 (VCC), U26.2 (+VIN); also elsewhere on the board
~RD: J7.4; also elsewhere on the board
~WR: J7.3; also elsewhere on the board

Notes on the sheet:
Power Supply and Extension Connector

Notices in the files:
KiCad/Radio-86RK-CRT-Mem.kicad_sch:
Licensed under CERN-OHL-S: https://cern-ohl.web.cern.ch
KiCad/Radio-86RK.kicad_pcb:
Copyright (C) 2020 - 2024 Sergey Kiselev
